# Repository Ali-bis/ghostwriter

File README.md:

🖋️ Ghost Writer - A Custom PCB Pen Plotter
Ghost Writer is a precision pen plotter that can be used to solve the "messy wiring" problem you usually get when you build one of those open-source plotter kits. To make that happen, I built a custom board that works with a compact - and 3D printed - parallel linkage gantry, which gives Ghost Writer high-torque motion control in a tiny footprint.

Figure 1: The Final Assembled Project, shown in CAD

🚀 Why I Did This
Most open-source kits have a problem with cable management and getting the electronics to work together without breaking. Ghost Writer was made to move away from the "breadboard prototype" stage and into something a bit more robust.

What I Wanted to Achieve:
No More Messy Wiring: A custom PCB means you can ditch the jumper wires and use dedicated traces for power and signal instead.
It's Super Compact: A custom 3D printed enclosure with a special cable management system keeps the whole thing at a tiny 30mm high.
It Draws Precisely: Powered by high-torque NEMA 17 steppers and a Seeed Studio XIAO (RP2040) for real-time inverse kinematics - that's a mouthful, but basically it draws very nicely.

🛠️ Hardware
Here are the key bits that make Ghost Writer tick
Main Processor: Seeed Studio XIAO RP2040 (a dual-core ARM Cortex M0+ processor)
Motion: 2x NEMA 17 Stepper Motors (each one with a 1.8° step angle for smooth movement)
Motor Drivers: 2x A4988 Stepper Drivers (these are super powerful and tuned to get the most out of the motors)
Pen Lift: a SG90 Micro Servo that you can control with a pulse-width modulation signal
Display: A tiny 0.96" I2C OLED Display so you can keep an eye on what's going on and where things are moving to
Power: 12V 2A DC via a standard barrel jack

🏗️ Mechanical Design & CAD
The enclosure was designed in Tinkercad with one main goal - stop the mechanical bits getting in the way of each other.
Carrier Board Mounting: the PCB is held in place with 9mm internal pillars which keeps it nice and insulated from the rest of the robot.
Parallel Linkage: the 80mm shoulder and 100mm forearm lengths give it a pretty generous drawing area for its size
U-Slot Management: a special cable path keeps the wiring clear of the moving parts
Figure 2: a clearance check between the custom PCB and the 3D printed housing

📂 Repository Structure
├── /hardware\
│   ├── /pcb        # the KiCad board files and Fabrication outputs (Gerbers)\
│   ├── /enclosure  # the STL files for the Box, Lid, and Linkage Arms\
│   └── /firmware   # the custom C++ validation suite (GhostWriter_Test)\
├── BOM.csv         # the Bill of Materials (itemised costs and links)\
└── README.md       # the Project documentation\

📋 Bill of Materials
The breakdown of costs and sourcing is in the BOM.csv file.
Note: This project tried to stay within a $100 budget by doing some creative 3D printing and choosing shipping methods that are pretty cost-effective

⚙️ Firmware
The system is currently running a custom C++ validation suite (GhostWriter_Test) to get the motors and servo working smoothly.
At the moment: I'm still working on getting G-Code interpretation via GRBL for RP2040 to work properly.
Motion Logic: the inverse kinematics calculations are being done on the second core of the RP2040 so the motor pulses are nice and smooth.
A Sneak Peek at the Design

Figure 2: Just to be sure - I checked to see if the PCB would fit inside the enclosure

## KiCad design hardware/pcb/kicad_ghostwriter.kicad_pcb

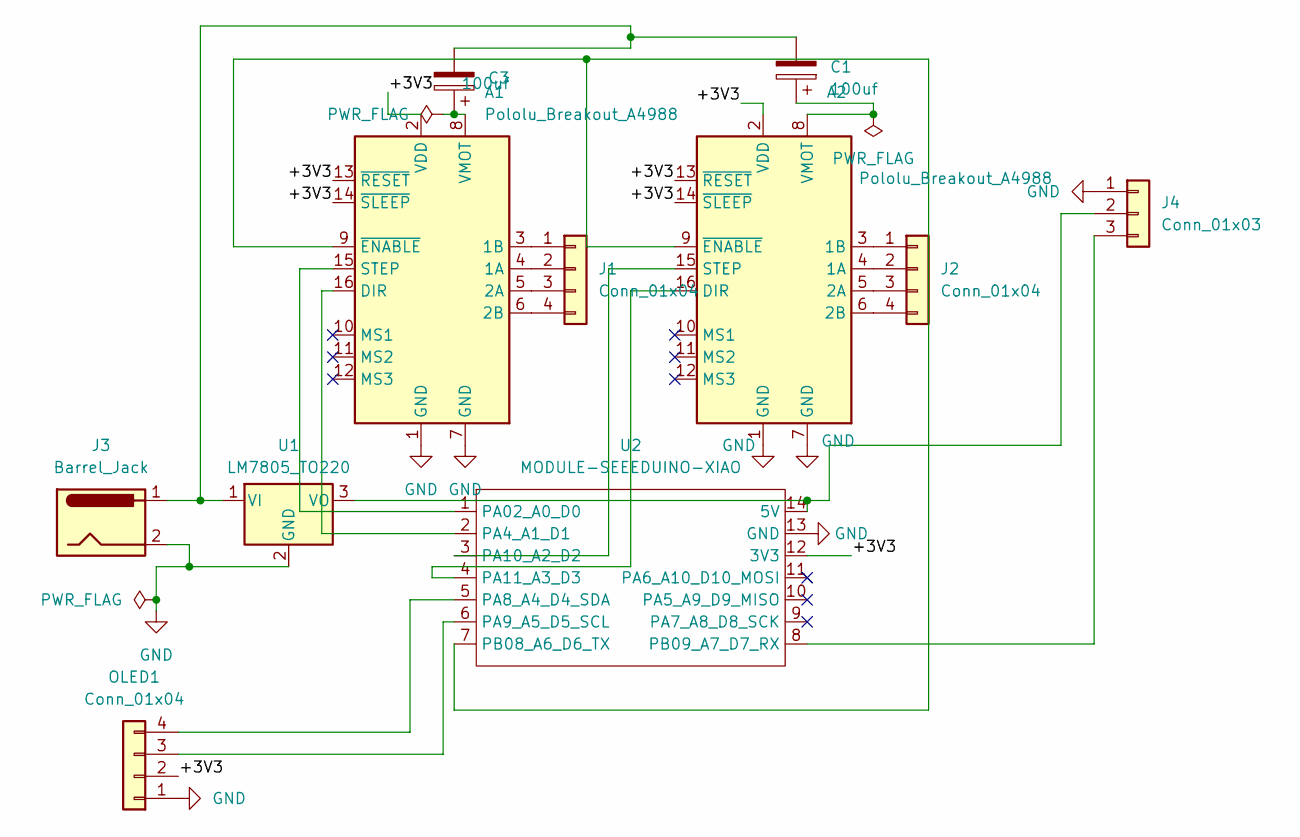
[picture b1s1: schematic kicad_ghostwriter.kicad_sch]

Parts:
A1, A2: Pololu_Breakout_A4988; Pololu_Breakout-16_15.2x20.3mm
C1, C3: 100uf; CP_Radial_D6.3mm_P2.50mm
J1, J2: Conn_01x04; PinHeader_1x04_P2.54mm_Vertical
J3: Barrel_Jack; BarrelJack_CUI_PJ-102AH_Horizontal
J4: Conn_01x03; PinHeader_1x03_P2.54mm_Vertical
OLED1: Conn_01x04; PinSocket_1x04_P2.54mm_Vertical
U1: LM7805_TO220; TO-220-3_Vertical
U2: MODULE-SEEEDUINO-XIAO; XIAO_RP2040_THT

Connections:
/+3V3: A1.2 (VDD), A1.13 (~RESET), A1.14 (~SLEEP), A2.2 (VDD), A2.13 (~RESET), A2.14 (~SLEEP), OLED1.2, U2.12 (3V3)
GND: A1.1 (GND), A1.7 (GND), A2.1 (GND), A2.7 (GND), J3.2, J4.1, OLED1.1, U1.2 (GND), U2.13 (GND)
unnamed: A1.4 (1A), J1.2
unnamed: A1.3 (1B), J1.1
unnamed: A1.5 (2A), J1.3
unnamed: A1.6 (2B), J1.4
unnamed: A1.16 (DIR), U2.2 (PA4_A1_D1)
unnamed: A1.15 (STEP), U2.1 (PA02_A0_D0)
unnamed: A1.8 (VMOT), C3.1
unnamed: A1.9 (~ENABLE), A2.9 (~ENABLE), U2.7 (PB08_A6_D6_TX)
unnamed: A2.4 (1A), J2.2
unnamed: A2.3 (1B), J2.1
unnamed: A2.5 (2A), J2.3
unnamed: A2.6 (2B), J2.4
unnamed: A2.16 (DIR), U2.4 (PA11_A3_D3)
unnamed: A2.15 (STEP), U2.3 (PA10_A2_D2)
unnamed: A2.8 (VMOT), C1.1
unnamed: J4.2, U1.3 (VO), U2.14 (5V)
unnamed: J4.3, U2.8 (PB09_A7_D7_RX)
unnamed: OLED1.3, U2.6 (PA9_A5_D5_SCL)
unnamed: OLED1.4, U2.5 (PA8_A4_D4_SDA)
unnamed: C1.2, C3.2, J3.1, U1.1 (VI)

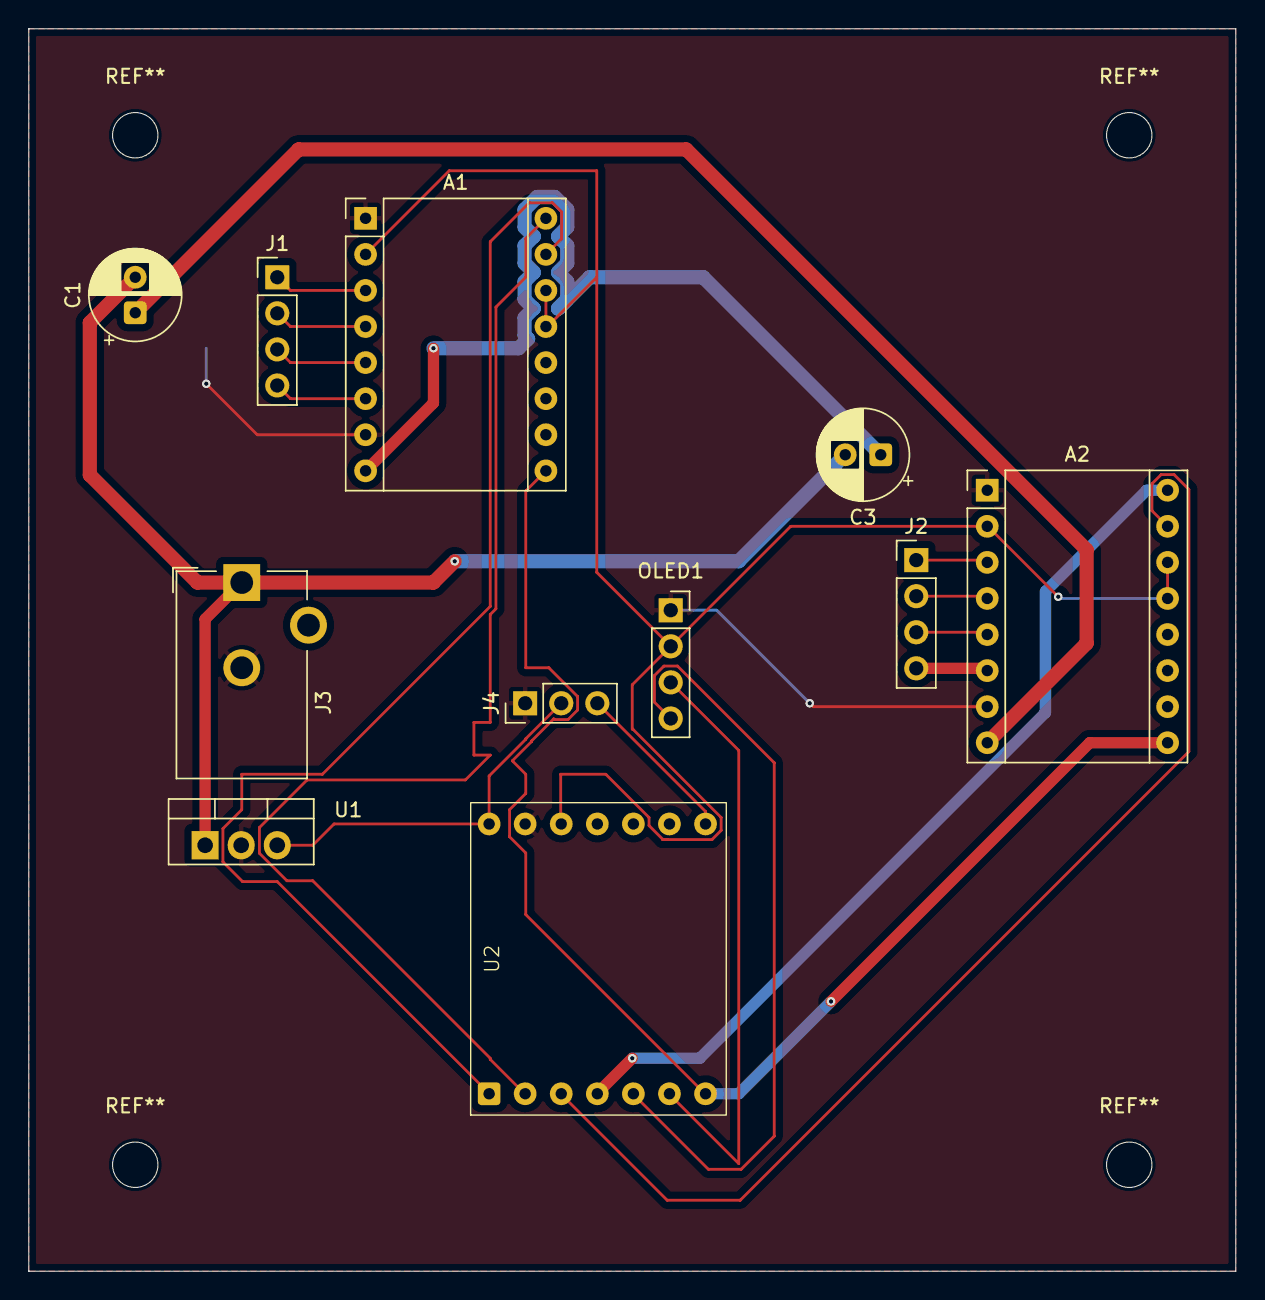
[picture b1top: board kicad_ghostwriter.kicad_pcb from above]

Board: 2 copper layers, 85.0 x 87.5 mm, 11 parts (0 on the bottom side), 22 nets.

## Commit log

2025-12-22 Rename hardware/pcb/hi.md to hardware/pcb/gerbers/hi.md
2025-12-22 Rename hardware/pcb/gerbers/hi.md to enclosure/stl
2025-12-22 Rename stl to st
2025-12-22 Rename enclosure/st to enclosure/stl/bobobob
2025-12-22 Rename bobobob to bobobo
2025-12-22 Rename enclosure/images/DesignCheckGW.png to hardware/enclosure/images/DesignCheckGW.png
2025-12-22 Rename enclosure/stl/Final_design_GW.stl to hardware/enclosure/stl/Final_design_GW.stl
2025-12-22 Create h
2025-12-22 Rename firmware/GhostWriterTest/GhostWriterTest.ino to hardware/firmware/GhostWriterTest/GhostWriterTest.ino
2025-12-22 Create hi
2025-12-22 Rename assemblypla.md to assemblyplan.md
2025-12-31 Rename Final_design_GW.stl to Final_design_GW (NOT TO BE PRINTED - ONLY REF OF FINAL MODEL) .stl
2025-12-31 Rename GW assembled vid.mp4 to GW_assembled_vid.mp4
